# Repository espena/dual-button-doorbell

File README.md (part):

# Dual-button doorbell

*V. 1.2*

A door bell that simply does more. Configurable with alarms, different sounds for the two buttons, bedtime LED indicator and timed notifications on specific days / hours. With audible 4Ω loudspeaker driven by a class D 3.2 W amplifier.

The project is described on my [home page](https://espenandersen.no/dual-button-doorbell/).

## Features

- Two-button interface with led indicators
- Personalized doorbell sound from custom wav files
- Cron calendar for scheduling sounds down to one second resolution
- SD card support for storing audio files and configuration
- WiFi interface with integrated antenna
- MQTT support for smart home integration and push notifications
- Battery backed-up real-time clock
- Time automatically set over the network using NTP
- Can be configured to use custom time zones
- Silent mode with alternate bell sounds during night hours
- Relay for triggering external doorbell along with custom sound
- Accepts AC or DC power input from existing doorbell power supplies

## Circuit

Custom symbols, footprints and 3D models can be found in [espena/kicad-libs](https://github.com/espena/kicad-libs) whenever they're ready.

## Firmware

Written in C/C++ using [FreeRTOS](https://www.freertos.org/) and [ESP-IDF](https://docs.espressif.com/projects/esp-idf/en/latest/esp32/get-started/). Additionally I use the brilliant [ccronexpr](https://github.com/staticlibs/ccronexpr) C library for parsing the cron-alike sound schedule. Source code is located in the [firmware/dual-button-doorbell](firmware/dual-button-doorbell) folder within this repository.

## Configuration

Configuration and assets must be stored on the SD card. See [/firmware/dual-button-doorbell/sdcard](/firmware/dual-button-doorbell/sdcard) for an example configuration.

## Button panel

## Panel back side enclosure

```stl
solid Mesh
  facet normal 0.000000 1.000000 0.000000
    outer loop
      vertex 50.000000 30.000000 0.000000
      vertex -50.000000 30.000000 0.000000
      vertex -50.000000 30.000000 19.000000
    endloop
  endfacet
  facet normal 0.000000 1.000000 -0.000000
    outer loop
      vertex 50.000000 30.000000 0.000000
      vertex -50.000000 30.000000 19.000000
      vertex 50.000000 30.000000 19.000000
    endloop
  endfacet
  facet normal -1.000000 -0.000000 0.000000
    outer loop
      vertex -50.000000 30.000000 19.000000
      vertex -50.000000 -30.000000 0.000000
      vertex -50.000000 -30.000000 19.000000
    endloop
  endfacet
  facet normal -1.000000 0.000000 0.000000
    outer loop
      vertex -50.000000 30.000000 0.000000
      vertex -50.000000 -30.000000 0.000000
      vertex -50.000000 30.000000 19.000000
    endloop
  endfacet
  facet normal 1.000000 -0.000000 0.000000
    outer loop
      vertex 50.000000 -30.000000 19.000000
      vertex 50.000000 30.000000 0.000000
      vertex 50.000000 30.000000 19.000000
    endloop
  endfacet
  facet normal 1.000000 0.000000 0.000000
    outer loop
      vertex 50.000000 -30.000000 0.000000
      vertex 50.000000 30.000000 0.000000
      vertex 50.000000 -30.000000 19.000000
    endloop
  endfacet
  facet normal 0.000000 0.000000 -1.000000
    outer loop
      vertex -48.000000 -28.000000 0.000000
      vertex -50.000000 30.000000 0.000000
      vertex -48.000000 28.000000 0.000000
    endloop
  endfacet
  facet normal 0.000000 0.000000 -1.000000
    outer loop
      vertex -50.000000 -30.000000 0.000000
      vertex -50.000000 30.000000 0.000000
      vertex -48.000000 -28.000000 0.000000
    endloop
  endfacet
  facet normal 0.000000 0.000000 -1.000000
    outer loop
      vertex -50.000000 -30.000000 0.000000
      vertex 48.000000 -28.000000 0.000000
      vertex 50.000000 -30.000000 0.000000
    endloop
  endfacet
  facet normal 0.000000 -0.000000 -1.000000
    outer loop
      vertex -48.000000 -28.000000 0.000000
      vertex 48.000000 -28.000000 0.000000
      vertex -50.000000 -30.000000 0.000000
    endloop
  endfacet
  facet normal 0.000000 0.000000 -1.000000
    outer loop
      vertex 48.000000 28.000000 0.000000
      vertex 50.000000 30.000000 0.000000
      vertex 48.000000 -28.000000 0.000000
    endloop
  endfacet
  facet normal 0.000000 0.000000 -1.000000
    outer loop
      vertex 48.000000 -28.000000 0.000000
      vertex 50.000000 30.000000 0.000000
      vertex 50.000000 -30.000000 0.000000
    endloop
  endfacet
  facet normal 0.000000 0.000000 -1.000000
    outer loop
      vertex -50.000000 30.000000 0.000000
      vertex 50.000000 30.000000 0.000000
      vertex -48.000000 28.000000 0.000000
    endloop
  endfacet
  facet normal 0.000000 0.000000 -1.000000
    outer loop
      vertex -48.000000 28.000000 0.000000
      vertex 50.000000 30.000000 0.000000
      vertex 48.000000 28.000000 0.000000
    endloop
  endfacet
  facet normal 0.000000 0.000000 1.000000
    outer loop
      vertex -29.796875 -7.549917 19.000000
      vertex -50.000000 -30.000000 19.000000
      vertex -29.410429 -7.946122 19.000000
    endloop
  endfacet
  facet normal 0.000000 0.000000 1.000000
    outer loop
      vertex -29.004713 -8.322572 19.000000
      vertex -29.410429 -7.946122 19.000000
      vertex -50.000000 -30.000000 19.000000
    endloop
  endfacet
  facet normal 0.000000 0.000000 1.000000
    outer loop
      vertex -30.163094 -7.134943 19.000000
      vertex -50.000000 -30.000000 19.000000
      vertex -29.796875 -7.549917 19.000000
    endloop
  endfacet
  facet normal 0.000000 0.000000 1.000000
    outer loop
      vertex -28.580736 -8.678329 19.000000
      vertex -29.004713 -8.322572 19.000000
      vertex -50.000000 -30.000000 19.000000
    endloop
  endfacet
  facet normal 0.000000 0.000000 1.000000
    outer loop
      vertex -30.508171 -6.702229 19.000000
      vertex -50.000000 -30.000000 19.000000
      vertex -30.163094 -7.134943 19.000000
    endloop
  endfacet
  facet normal 0.000000 0.000000 1.000000
    outer loop
      vertex -28.139555 -9.012512 19.000000
      vertex -28.580736 -8.678329 19.000000
      vertex -50.000000 -30.000000 19.000000
    endloop
  endfacet
  facet normal 0.000000 0.000000 1.000000
    outer loop
      vertex -30.831251 -6.252852 19.000000
      vertex -50.000000 -30.000000 19.000000
      vertex -30.508171 -6.702229 19.000000
    endloop
  endfacet
  facet normal 0.000000 0.000000 1.000000
    outer loop
      vertex -27.682264 -9.324287 19.000000
      vertex -28.139555 -9.012512 19.000000
      vertex -50.000000 -30.000000 19.000000
    endloop
  endfacet
  facet normal 0.000000 0.000000 1.000000
    outer loop
      vertex -31.131529 -5.787931 19.000000
      vertex -50.000000 -30.000000 19.000000
      vertex -30.831251 -6.252852 19.000000
    endloop
  endfacet
  facet normal 0.000000 0.000000 1.000000
    outer loop
      vertex -27.209999 -9.612882 19.000000
      vertex -27.682264 -9.324287 19.000000
      vertex -50.000000 -30.000000 19.000000
    endloop
  endfacet
  facet normal 0.000000 0.000000 1.000000
    outer loop
      vertex -31.408260 -5.308619 19.000000
      vertex -50.000000 -30.000000 19.000000
      vertex -31.131529 -5.787931 19.000000
    endloop
  endfacet
  facet normal 0.000000 0.000000 1.000000
    outer loop
      vertex -26.723938 -9.877577 19.000000
      vertex -27.209999 -9.612882 19.000000
      vertex -50.000000 -30.000000 19.000000
    endloop
  endfacet
  facet normal 0.000000 0.000000 1.000000
    outer loop
      vertex -31.660755 -4.816110 19.000000
      vertex -50.000000 -30.000000 19.000000
      vertex -31.408260 -5.308619 19.000000
    endloop
  endfacet
  facet normal 0.000000 0.000000 1.000000
    outer loop
      vertex -26.225286 -10.117715 19.000000
      vertex -26.723938 -9.877577 19.000000
      vertex -50.000000 -30.000000 19.000000
    endloop
  endfacet
  facet normal 0.000000 0.000000 1.000000
    outer loop
      vertex -31.888386 -4.311626 19.000000
      vertex -50.000000 -30.000000 19.000000
      vertex -31.660755 -4.816110 19.000000
    endloop
  endfacet
  facet normal 0.000000 0.000000 1.000000
    outer loop
      vertex -25.715286 -10.332699 19.000000
      vertex -26.225286 -10.117715 19.000000
      vertex -50.000000 -30.000000 19.000000
    endloop
  endfacet
  facet normal 0.000000 0.000000 1.000000
    outer loop
      vertex -32.090588 -3.796424 19.000000
      vertex -50.000000 -30.000000 19.000000
      vertex -31.888386 -4.311626 19.000000
    endloop
  endfacet
  facet normal 0.000000 0.000000 1.000000
    outer loop
      vertex -25.195202 -10.521994 19.000000
      vertex -25.715286 -10.332699 19.000000
      vertex -50.000000 -30.000000 19.000000
    endloop
  endfacet
  facet normal 0.000000 0.000000 1.000000
    outer loop
      vertex -32.266857 -3.271782 19.000000
      vertex -50.000000 -30.000000 19.000000
      vertex -32.090588 -3.796424 19.000000
    endloop
  endfacet
  facet normal 0.000000 0.000000 1.000000
    outer loop
      vertex -24.666328 -10.685129 19.000000
      vertex -25.195202 -10.521994 19.000000
      vertex -50.000000 -30.000000 19.000000
    endloop
  endfacet
  facet normal 0.000000 0.000000 1.000000
    outer loop
      vertex -32.416759 -2.739007 19.000000
      vertex -50.000000 -30.000000 19.000000
      vertex -32.266857 -3.271782 19.000000
    endloop
  endfacet
  facet normal 0.000000 0.000000 1.000000
    outer loop
      vertex -24.129982 -10.821700 19.000000
      vertex -24.666328 -10.685129 19.000000
      vertex -50.000000 -30.000000 19.000000
    endloop
  endfacet
  facet normal 0.000000 0.000000 1.000000
    outer loop
      vertex -32.539913 -2.199422 19.000000
      vertex -50.000000 -30.000000 19.000000
      vertex -32.416759 -2.739007 19.000000
    endloop
  endfacet
  facet normal 0.000000 0.000000 1.000000
    outer loop
      vertex -23.587494 -10.931366 19.000000
      vertex -24.129982 -10.821700 19.000000
      vertex -50.000000 -30.000000 19.000000
    endloop
  endfacet
  facet normal 0.000000 0.000000 1.000000
    outer loop
      vertex -32.636021 -1.654369 19.000000
      vertex -50.000000 -30.000000 19.000000
      vertex -32.539913 -2.199422 19.000000
    endloop
  endfacet
  facet normal 0.000000 0.000000 1.000000
    outer loop
      vertex -23.040215 -11.013855 19.000000
      vertex -23.587494 -10.931366 19.000000
      vertex -50.000000 -30.000000 19.000000
    endloop
  endfacet
  facet normal 0.000000 0.000000 1.000000
    outer loop
      vertex -32.704842 -1.105203 19.000000
      vertex -50.000000 -30.000000 19.000000
      vertex -32.636021 -1.654369 19.000000
    endloop
  endfacet
  facet normal 0.000000 0.000000 1.000000
    outer loop
      vertex -22.489504 -11.068962 19.000000
      vertex -23.040215 -11.013855 19.000000
      vertex -50.000000 -30.000000 19.000000
    endloop
  endfacet
  facet normal 0.000000 0.000000 1.000000
    outer loop
      vertex -32.746201 -0.553289 19.000000
      vertex -50.000000 -30.000000 19.000000
      vertex -32.704842 -1.105203 19.000000
    endloop
  endfacet
  facet normal 0.000000 0.000000 1.000000
    outer loop
      vertex -21.936731 -11.096550 19.000000
      vertex -22.489504 -11.068962 19.000000
      vertex -50.000000 -30.000000 19.000000
    endloop
  endfacet
  facet normal 0.000000 0.000000 1.000000
    outer loop
      vertex -32.759998 0.000000 19.000000
      vertex -50.000000 -30.000000 19.000000
      vertex -32.746201 -0.553289 19.000000
    endloop
  endfacet
  facet normal 0.000000 0.000000 1.000000
    outer loop
      vertex -21.383270 -11.096550 19.000000
      vertex -21.936731 -11.096550 19.000000
      vertex -50.000000 -30.000000 19.000000
    endloop
  endfacet
  facet normal 0.000000 0.000000 1.000000
    outer loop
      vertex -20.830496 -11.068962 19.000000
      vertex -21.383270 -11.096550 19.000000
      vertex -50.000000 -30.000000 19.000000
    endloop
  endfacet
  facet normal 0.000000 0.000000 1.000000
    outer loop
      vertex -20.279785 -11.013855 19.000000
      vertex -20.830496 -11.068962 19.000000
      vertex -50.000000 -30.000000 19.000000
    endloop
  endfacet
  facet normal 0.000000 0.000000 1.000000
    outer loop
      vertex -19.732506 -10.931366 19.000000
      vertex -20.279785 -11.013855 19.000000
      vertex -50.000000 -30.000000 19.000000
    endloop
  endfacet
  facet normal 0.000000 0.000000 1.000000
    outer loop
      vertex -19.190018 -10.821700 19.000000
      vertex -19.732506 -10.931366 19.000000
      vertex -50.000000 -30.000000 19.000000
    endloop
  endfacet
  facet normal 0.000000 0.000000 1.000000
    outer loop
      vertex -18.653671 -10.685129 19.000000
      vertex -19.190018 -10.821700 19.000000
      vertex -50.000000 -30.000000 19.000000
    endloop
  endfacet
  facet normal 0.000000 0.000000 1.000000
    outer loop
      vertex -50.000000 30.000000 19.000000
      vertex -50.000000 -30.000000 19.000000
      vertex -32.759998 0.000000 19.000000
    endloop
  endfacet
  facet normal 0.000000 0.000000 1.000000
    outer loop
      vertex -50.000000 30.000000 19.000000
      vertex -32.759998 0.000000 19.000000
      vertex -32.746201 0.553289 19.000000
    endloop
  endfacet
  facet normal 0.000000 0.000000 1.000000
    outer loop
      vertex -50.000000 30.000000 19.000000
      vertex -32.746201 0.553289 19.000000
      vertex -32.704842 1.105203 19.000000
    endloop
  endfacet
  facet normal 0.000000 0.000000 1.000000
    outer loop
      vertex -50.000000 30.000000 19.000000
      vertex -32.704842 1.105203 19.000000
      vertex -32.636021 1.654369 19.000000
    endloop
  endfacet
  facet normal 0.000000 0.000000 1.000000
    outer loop
      vertex -50.000000 30.000000 19.000000
      vertex -32.636021 1.654369 19.000000
      vertex -32.539913 2.199422 19.000000
    endloop
  endfacet
  facet normal 0.000000 0.000000 1.000000
    outer loop
      vertex -50.000000 30.000000 19.000000
      vertex -32.539913 2.199422 19.000000
      vertex -32.416759 2.739007 19.000000
    endloop
  endfacet
  facet normal 0.000000 0.000000 1.000000
    outer loop
      vertex -50.000000 30.000000 19.000000
      vertex -32.416759 2.739007 19.000000
      vertex -32.266857 3.271782 19.000000
    endloop
  endfacet
  facet normal 0.000000 0.000000 1.000000
    outer loop
      vertex -50.000000 30.000000 19.000000
      vertex -32.266857 3.271782 19.000000
      vertex -32.090588 3.796424 19.000000
    endloop
  endfacet
  facet normal 0.000000 0.000000 1.000000
    outer loop
      vertex -50.000000 30.000000 19.000000
      vertex -32.090588 3.796424 19.000000
      vertex -31.888386 4.311626 19.000000
    endloop
  endfacet
  facet normal 0.000000 0.000000 1.000000
    outer loop
      vertex -50.000000 30.000000 19.000000
      vertex -31.888386 4.311626 19.000000
      vertex -31.660755 4.816110 19.000000
    endloop
  endfacet
  facet normal 0.000000 0.000000 1.000000
    outer loop
      vertex -50.000000 30.000000 19.000000
      vertex -31.660755 4.816110 19.000000
      vertex -31.408260 5.308619 19.000000
    endloop
  endfacet
  facet normal 0.000000 0.000000 1.000000
    outer loop
      vertex -50.000000 30.000000 19.000000
      vertex -31.408260 5.308619 19.000000
      vertex -31.131529 5.787931 19.000000
    endloop
  endfacet
  facet normal 0.000000 0.000000 1.000000
    outer loop
      vertex -50.000000 30.000000 19.000000
      vertex -31.131529 5.787931 19.000000
      vertex -30.831251 6.252852 19.000000
    endloop
  endfacet
  facet normal 0.000000 0.000000 1.000000
    outer loop
      vertex -50.000000 30.000000 19.000000
      vertex -30.831251 6.252852 19.000000
      vertex -30.508171 6.702229 19.000000
    endloop
  endfacet
  facet normal 0.000000 0.000000 1.000000
    outer loop
      vertex -50.000000 30.000000 19.000000
      vertex -30.508171 6.702229 19.000000
      vertex -30.163094 7.134943 19.000000
    endloop
  endfacet
  facet normal 0.000000 0.000000 1.000000
    outer loop
      vertex -50.000000 30.000000 19.000000
      vertex -30.163094 7.134943 19.000000
      vertex -29.796875 7.549917 19.000000
    endloop
  endfacet
  facet normal 0.000000 0.000000 1.000000
    outer loop
      vertex -50.000000 30.000000 19.000000
      vertex -29.796875 7.549917 19.000000
      vertex -29.410429 7.946122 19.000000
    endloop
  endfacet
  facet normal 0.000000 0.000000 1.000000
    outer loop
      vertex -50.000000 30.000000 19.000000
      vertex -29.410429 7.946122 19.000000
      vertex -29.004713 8.322572 19.000000
    endloop
  endfacet
  facet normal 0.000000 0.000000 1.000000
    outer loop
      vertex -28.580736 8.678329 19.000000
      vertex -50.000000 30.000000 19.000000
      vertex -29.004713 8.322572 19.000000
    endloop
  endfacet
  facet normal 0.000000 0.000000 1.000000
    outer loop
      vertex -28.139555 9.012512 19.000000
      vertex -50.000000 30.000000 19.000000
      vertex -28.580736 8.678329 19.000000
    endloop
  endfacet
  facet normal 0.000000 0.000000 1.000000
    outer loop
      vertex -27.682264 9.324287 19.000000
      vertex -50.000000 30.000000 19.000000
      vertex -28.139555 9.012512 19.000000
    endloop
  endfacet
  facet normal 0.000000 0.000000 1.000000
    outer loop
      vertex -27.209999 9.612882 19.000000
      vertex -50.000000 30.000000 19.000000
      vertex -27.682264 9.324287 19.000000
    endloop
  endfacet
  facet normal 0.000000 0.000000 1.000000
    outer loop
      vertex -26.723938 9.877577 19.000000
      vertex -50.000000 30.000000 19.000000
      vertex -27.209999 9.612882 19.000000
    endloop
  endfacet
  facet normal 0.000000 0.000000 1.000000
    outer loop
      vertex -26.225286 10.117715 19.000000
      vertex -50.000000 30.000000 19.000000
      vertex -26.723938 9.877577 19.000000
    endloop
  endfacet
  facet normal 0.000000 0.000000 1.000000
    outer loop
      vertex -25.715286 10.332699 19.000000
      vertex -50.000000 30.000000 19.000000
      vertex -26.225286 10.117715 19.000000
    endloop
  endfacet
  facet normal 0.000000 0.000000 1.000000
    outer loop
      vertex -25.195202 10.521994 19.000000
      vertex -50.000000 30.000000 19.000000
      vertex -25.715286 10.332699 19.000000
    endloop
  endfacet
  facet normal 0.000000 0.000000 1.000000
    outer loop
      vertex -24.666328 10.685129 19.000000
      vertex -50.000000 30.000000 19.000000
      vertex -25.195202 10.521994 19.000000
    endloop
  endfacet
  facet normal 0.000000 0.000000 1.000000
    outer loop
      vertex -24.129982 10.821700 19.000000
      vertex -50.000000 30.000000 19.000000
      vertex -24.666328 10.685129 19.000000
    endloop
  endfacet
  facet normal 0.000000 0.000000 1.000000
    outer loop
      vertex -23.587494 10.931366 19.000000
      vertex -50.000000 30.000000 19.000000
      vertex -24.129982 10.821700 19.000000
    endloop
  endfacet
  facet normal 0.000000 0.000000 1.000000
    outer loop
      vertex -23.040215 11.013855 19.000000
      vertex -50.000000 30.000000 19.000000
      vertex -23.587494 10.931366 19.000000
    endloop
  endfacet
  facet normal 0.000000 0.000000 1.000000
    outer loop
      vertex -22.489504 11.068962 19.000000
      vertex -50.000000 30.000000 19.000000
      vertex -23.040215 11.013855 19.000000
    endloop
  endfacet
  facet normal 0.000000 0.000000 1.000000
    outer loop
      vertex -21.936731 11.096550 19.000000
      vertex -50.000000 30.000000 19.000000
      vertex -22.489504 11.068962 19.000000
    endloop
  endfacet
  facet normal 0.000000 0.000000 1.000000
    outer loop
      vertex -21.383270 11.096550 19.000000
      vertex -50.000000 30.000000 19.000000
      vertex -21.936731 11.096550 19.000000
    endloop
  endfacet
  facet normal 0.000000 0.000000 1.000000
    outer loop
      vertex -20.830496 11.068962 19.000000
      vertex -50.000000 30.000000 19.000000
      vertex -21.383270 11.096550 19.000000
    endloop
  endfacet
  facet normal 0.000000 0.000000 1.000000
    outer loop
      vertex -20.279785 11.013855 19.000000
      vertex -50.000000 30.000000 19.000000
      vertex -20.830496 11.068962 19.000000
    endloop
  endfacet
  facet normal 0.000000 0.000000 1.000000
    outer loop
      vertex -19.732506 10.931366 19.000000
      vertex -50.000000 30.000000 19.000000
      vertex -20.279785 11.013855 19.000000
    endloop
  endfacet
  facet normal 0.000000 0.000000 1.000000
    outer loop
      vertex -19.190018 10.821700 19.000000
      vertex -50.000000 30.000000 19.000000
      vertex -19.732506 10.931366 19.000000
    endloop
  endfacet
  facet normal 0.000000 0.000000 1.000000
    outer loop
      vertex 13.522124 -7.549917 19.000000
      vertex -13.909572 -7.946122 19.000000
      vertex 13.908571 -7.946122 19.000000
    endloop
  endfacet
  facet normal 0.000000 0.000000 1.000000
    outer loop
      vertex 13.522124 -7.549917 19.000000
      vertex -13.523125 -7.549917 19.000000
      vertex -13.909572 -7.946122 19.000000
    endloop
  endfacet
  facet normal 0.000000 0.000000 1.000000
    outer loop
      vertex 14.314287 -8.322572 19.000000
      vertex 13.908571 -7.946122 19.000000
      vertex -13.909572 -7.946122 19.000000
    endloop
  endfacet
  facet normal 0.000000 0.000000 1.000000
    outer loop
      vertex 14.314287 -8.322572 19.000000
      vertex -13.909572 -7.946122 19.000000
      vertex -14.315288 -8.322572 19.000000
    endloop
  endfacet
  facet normal 0.000000 0.000000 1.000000
    outer loop
      vertex 14.314287 -8.322572 19.000000
      vertex -14.315288 -8.322572 19.000000
      vertex -14.739264 -8.678329 19.000000
    endloop
  endfacet
  facet normal 0.000000 0.000000 1.000000
    outer loop
      vertex 13.155907 -7.134943 19.000000
      vertex -12.811830 -6.702229 19.000000
      vertex -13.156907 -7.134943 19.000000
    endloop
  endfacet
  facet normal 0.000000 0.000000 1.000000
    outer loop
      vertex 13.155907 -7.134943 19.000000
      vertex -13.156907 -7.134943 19.000000
      vertex -13.523125 -7.549917 19.000000
    endloop
  endfacet
  facet normal 0.000000 0.000000 1.000000
    outer loop
      vertex 13.155907 -7.134943 19.000000
      vertex -13.523125 -7.549917 19.000000
      vertex 13.522124 -7.549917 19.000000
    endloop
  endfacet
  facet normal 0.000000 0.000000 1.000000
    outer loop
      vertex 14.738263 -8.678329 19.000000
      vertex 14.314287 -8.322572 19.000000
      vertex -14.739264 -8.678329 19.000000
    endloop
  endfacet
  facet normal 0.000000 0.000000 1.000000
    outer loop
      vertex 12.810829 -6.702229 19.000000
      vertex -12.811830 -6.702229 19.000000
      vertex 13.155907 -7.134943 19.000000
    endloop
  endfacet
  facet normal 0.000000 0.000000 1.000000
    outer loop
      vertex 15.179445 -9.012512 19.000000
      vertex -14.739264 -8.678329 19.000000
      vertex -15.180446 -9.012512 19.000000
    endloop
  endfacet
  facet normal 0.000000 0.000000 1.000000
    outer loop
      vertex 15.179445 -9.012512 19.000000
      vertex -15.180446 -9.012512 19.000000
      vertex -15.637736 -9.324287 19.000000
    endloop
  endfacet
  facet normal 0.000000 0.000000 1.000000
    outer loop
      vertex 15.179445 -9.012512 19.000000
      vertex 14.738263 -8.678329 19.000000
      vertex -14.739264 -8.678329 19.000000
    endloop
  endfacet
  facet normal 0.000000 0.000000 1.000000
    outer loop
      vertex 12.487750 -6.252852 19.000000
      vertex -12.488750 -6.252852 19.000000
      vertex -12.811830 -6.702229 19.000000
    endloop
  endfacet
  facet normal 0.000000 0.000000 1.000000
    outer loop
      vertex 12.487750 -6.252852 19.000000
      vertex -12.811830 -6.702229 19.000000
      vertex 12.810829 -6.702229 19.000000
    endloop
  endfacet
  facet normal 0.000000 0.000000 1.000000
    outer loop
      vertex 15.636737 -9.324287 19.000000
      vertex 15.179445 -9.012512 19.000000
      vertex -15.637736 -9.324287 19.000000
    endloop
  endfacet
  facet normal 0.000000 0.000000 1.000000
    outer loop
      vertex 12.187471 -5.787931 19.000000
      vertex -11.911740 -5.308619 19.000000
      vertex -12.188471 -5.787931 19.000000
    endloop
  endfacet
  facet normal 0.000000 0.000000 1.000000
    outer loop
      vertex 12.187471 -5.787931 19.000000
      vertex -12.188471 -5.787931 19.000000
      vertex -12.488750 -6.252852 19.000000
    endloop
  endfacet
  facet normal 0.000000 0.000000 1.000000
    outer loop
      vertex 12.187471 -5.787931 19.000000
      vertex -12.488750 -6.252852 19.000000
      vertex 12.487750 -6.252852 19.000000
    endloop
  endfacet
  facet normal 0.000000 0.000000 1.000000
    outer loop
      vertex 16.108999 -9.612882 19.000000
      vertex -15.637736 -9.324287 19.000000
      vertex -16.110001 -9.612882 19.000000
    endloop
  endfacet
  facet normal 0.000000 0.000000 1.000000
    outer loop
      vertex 16.108999 -9.612882 19.000000
      vertex 15.636737 -9.324287 19.000000
      vertex -15.637736 -9.324287 19.000000
    endloop
  endfacet
  facet normal 0.000000 0.000000 1.000000
    outer loop
      vertex 11.910741 -5.308619 19.000000
      vertex -11.911740 -5.308619 19.000000
      vertex 12.187471 -5.787931 19.000000
    endloop
  endfacet
  facet normal 0.000000 0.000000 1.000000
    outer loop
      vertex 16.595062 -9.877577 19.000000
      vertex 16.108999 -9.612882 19.000000
      vertex -16.110001 -9.612882 19.000000
    endloop
  endfacet
  facet normal 0.000000 0.000000 1.000000
    outer loop
      vertex 16.595062 -9.877577 19.000000
      vertex -16.110001 -9.612882 19.000000
      vertex -16.596062 -9.877577 19.000000
    endloop
  endfacet
  facet normal 0.000000 0.000000 1.000000
    outer loop
      vertex 11.658246 -4.816110 19.000000
      vertex -11.659245 -4.816110 19.000000
      vertex -11.911740 -5.308619 19.000000
    endloop
  endfacet
  facet normal 0.000000 0.000000 1.000000
    outer loop
      vertex 11.658246 -4.816110 19.000000
      vertex -11.911740 -5.308619 19.000000
      vertex 11.910741 -5.308619 19.000000
    endloop
  endfacet
  facet normal 0.000000 0.000000 1.000000
    outer loop
      vertex 17.093714 -10.117715 19.000000
      vertex -16.596062 -9.877577 19.000000
      vertex -17.094713 -10.117715 19.000000
    endloop
  endfacet
  facet normal 0.000000 0.000000 1.000000
    outer loop
      vertex 17.093714 -10.117715 19.000000
      vertex 16.595062 -9.877577 19.000000
      vertex -16.596062 -9.877577 19.000000
    endloop
  endfacet
  facet normal 0.000000 0.000000 1.000000
    outer loop
      vertex 11.430614 -4.311626 19.000000
      vertex -11.431614 -4.311626 19.000000
      vertex -11.659245 -4.816110 19.000000
    endloop
  endfacet
  facet normal 0.000000 0.000000 1.000000
    outer loop
      vertex 11.430614 -4.311626 19.000000
      vertex -11.659245 -4.816110 19.000000
      vertex 11.658246 -4.816110 19.000000
    endloop
  endfacet
  facet normal 0.000000 0.000000 1.000000
    outer loop
      vertex 17.603714 -10.332699 19.000000
      vertex -17.094713 -10.117715 19.000000
      vertex -17.604715 -10.332699 19.000000
    endloop
  endfacet
  facet normal 0.000000 0.000000 1.000000
    outer loop
      vertex 17.603714 -10.332699 19.000000
      vertex 17.093714 -10.117715 19.000000
      vertex -17.094713 -10.117715 19.000000
    endloop
  endfacet
  facet normal 0.000000 0.000000 1.000000
    outer loop
      vertex 11.228412 -3.796424 19.000000
      vertex -11.053142 -3.271782 19.000000
      vertex -11.229412 -3.796424 19.000000
    endloop
  endfacet
  facet normal 0.000000 0.000000 1.000000
    outer loop
      vertex 11.228412 -3.796424 19.000000
      vertex -11.229412 -3.796424 19.000000
      vertex -11.431614 -4.311626 19.000000
    endloop
  endfacet
  facet normal 0.000000 0.000000 1.000000
    outer loop
      vertex 11.228412 -3.796424 19.000000
      vertex -11.431614 -4.311626 19.000000
      vertex 11.430614 -4.311626 19.000000
    endloop
  endfacet
  facet normal 0.000000 0.000000 1.000000
    outer loop
      vertex 18.123798 -10.521994 19.000000
      vertex -17.604715 -10.332699 19.000000
      vertex -18.124798 -10.521994 19.000000
    endloop
  endfacet
  facet normal 0.000000 0.000000 1.000000
    outer loop
      vertex 18.123798 -10.521994 19.000000
      vertex 17.603714 -10.332699 19.000000
      vertex -17.604715 -10.332699 19.000000
    endloop
  endfacet
  facet normal 0.000000 0.000000 1.000000
    outer loop
      vertex 11.052142 -3.271782 19.000000
      vertex -11.053142 -3.271782 19.000000
      vertex 11.228412 -3.796424 19.000000
    endloop
  endfacet
  facet normal 0.000000 0.000000 1.000000
    outer loop
      vertex 18.652670 -10.685129 19.000000
      vertex -18.124798 -10.521994 19.000000
      vertex -18.653671 -10.685129 19.000000
    endloop
  endfacet
  facet normal 0.000000 0.000000 1.000000
    outer loop
      vertex 18.652670 -10.685129 19.000000
      vertex -18.653671 -10.685129 19.000000
      vertex -50.000000 -30.000000 19.000000
    endloop
  endfacet
  facet normal 0.000000 0.000000 1.000000
    outer loop
      vertex 18.652670 -10.685129 19.000000
      vertex 18.123798 -10.521994 19.000000
      vertex -18.124798 -10.521994 19.000000
    endloop
  endfacet
  facet normal 0.000000 0.000000 1.000000
    outer loop
      vertex 10.902242 -2.739007 19.000000
      vertex -10.903242 -2.739007 19.000000
      vertex -11.053142 -3.271782 19.000000
    endloop
  endfacet
  facet normal 0.000000 0.000000 1.000000
    outer loop
      vertex 10.902242 -2.739007 19.000000
      vertex -11.053142 -3.271782 19.000000
      vertex 11.052142 -3.271782 19.000000
    endloop
  endfacet
  facet normal 0.000000 0.000000 1.000000
    outer loop
      vertex 10.779085 -2.199422 19.000000
      vertex -10.780086 -2.199422 19.000000
      vertex -10.903242 -2.739007 19.000000
    endloop
  endfacet
  facet normal 0.000000 0.000000 1.000000
    outer loop
      vertex 10.779085 -2.199422 19.000000
      vertex -10.903242 -2.739007 19.000000
      vertex 10.902242 -2.739007 19.000000
    endloop
  endfacet
  facet normal 0.000000 0.000000 1.000000
    outer loop
      vertex 10.682978 -1.654369 19.000000
      vertex -10.683978 -1.654369 19.000000
      vertex -10.780086 -2.199422 19.000000
    endloop
  endfacet
  facet normal 0.000000 0.000000 1.000000
    outer loop
      vertex 10.682978 -1.654369 19.000000
      vertex -10.780086 -2.199422 19.000000
      vertex 10.779085 -2.199422 19.000000
    endloop
  endfacet
  facet normal 0.000000 0.000000 1.000000
    outer loop
      vertex 10.614159 -1.105203 19.000000
      vertex -10.573798 -0.553289 19.000000
      vertex -10.615158 -1.105203 19.000000
    endloop
  endfacet
  facet normal 0.000000 0.000000 1.000000
    outer loop
      vertex 10.614159 -1.105203 19.000000
      vertex -10.615158 -1.105203 19.000000
      vertex -10.683978 -1.654369 19.000000
    endloop
  endfacet
  facet normal 0.000000 0.000000 1.000000
    outer loop
      vertex 10.614159 -1.105203 19.000000
      vertex -10.683978 -1.654369 19.000000
      vertex 10.682978 -1.654369 19.000000
    endloop
  endfacet
  facet normal 0.000000 0.000000 1.000000
    outer loop
      vertex 10.572798 -0.553289 19.000000
      vertex -10.573798 -0.553289 19.000000
      vertex 10.614159 -1.105203 19.000000
    endloop
  endfacet
  facet normal 0.000000 0.000000 1.000000
    outer loop
      vertex 10.559000 0.000000 19.000000
      vertex -10.573798 -0.553289 19.000000
      vertex 10.572798 -0.553289 19.000000
    endloop
  endfacet
  facet normal 0.000000 0.000000 1.000000
    outer loop
      vertex 10.559000 0.000000 19.000000
      vertex -10.560000 0.000000 19.000000
      vertex -10.573798 -0.553289 19.000000
    endloop
  endfacet
  facet normal 0.000000 0.000000 1.000000
    outer loop
      vertex 10.572798 0.553289 19.000000
      vertex -10.573798 0.553289 19.000000
      vertex -10.560000 0.000000 19.000000
    endloop
  endfacet
  facet normal 0.000000 0.000000 1.000000
    outer loop
      vertex 10.572798 0.553289 19.000000
      vertex -10.560000 0.000000 19.000000
      vertex 10.559000 0.000000 19.000000
    endloop
  endfacet
  facet normal 0.000000 0.000000 1.000000
    outer loop
      vertex 10.614159 1.105203 19.000000
      vertex -10.683978 1.654369 19.000000
      vertex -10.615158 1.105203 19.000000
    endloop
  endfacet
  facet normal 0.000000 0.000000 1.000000
    outer loop
      vertex 10.614159 1.105203 19.000000
      vertex -10.615158 1.105203 19.000000
      vertex -10.573798 0.553289 19.000000
    endloop
  endfacet
  facet normal 0.000000 0.000000 1.000000
    outer loop
      vertex 10.614159 1.105203 19.000000
      vertex -10.573798 0.553289 19.000000
      vertex 10.572798 0.553289 19.000000
    endloop
  endfacet
  facet normal 0.000000 0.000000 1.000000
    outer loop
      vertex 10.682978 1.654369 19.000000
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
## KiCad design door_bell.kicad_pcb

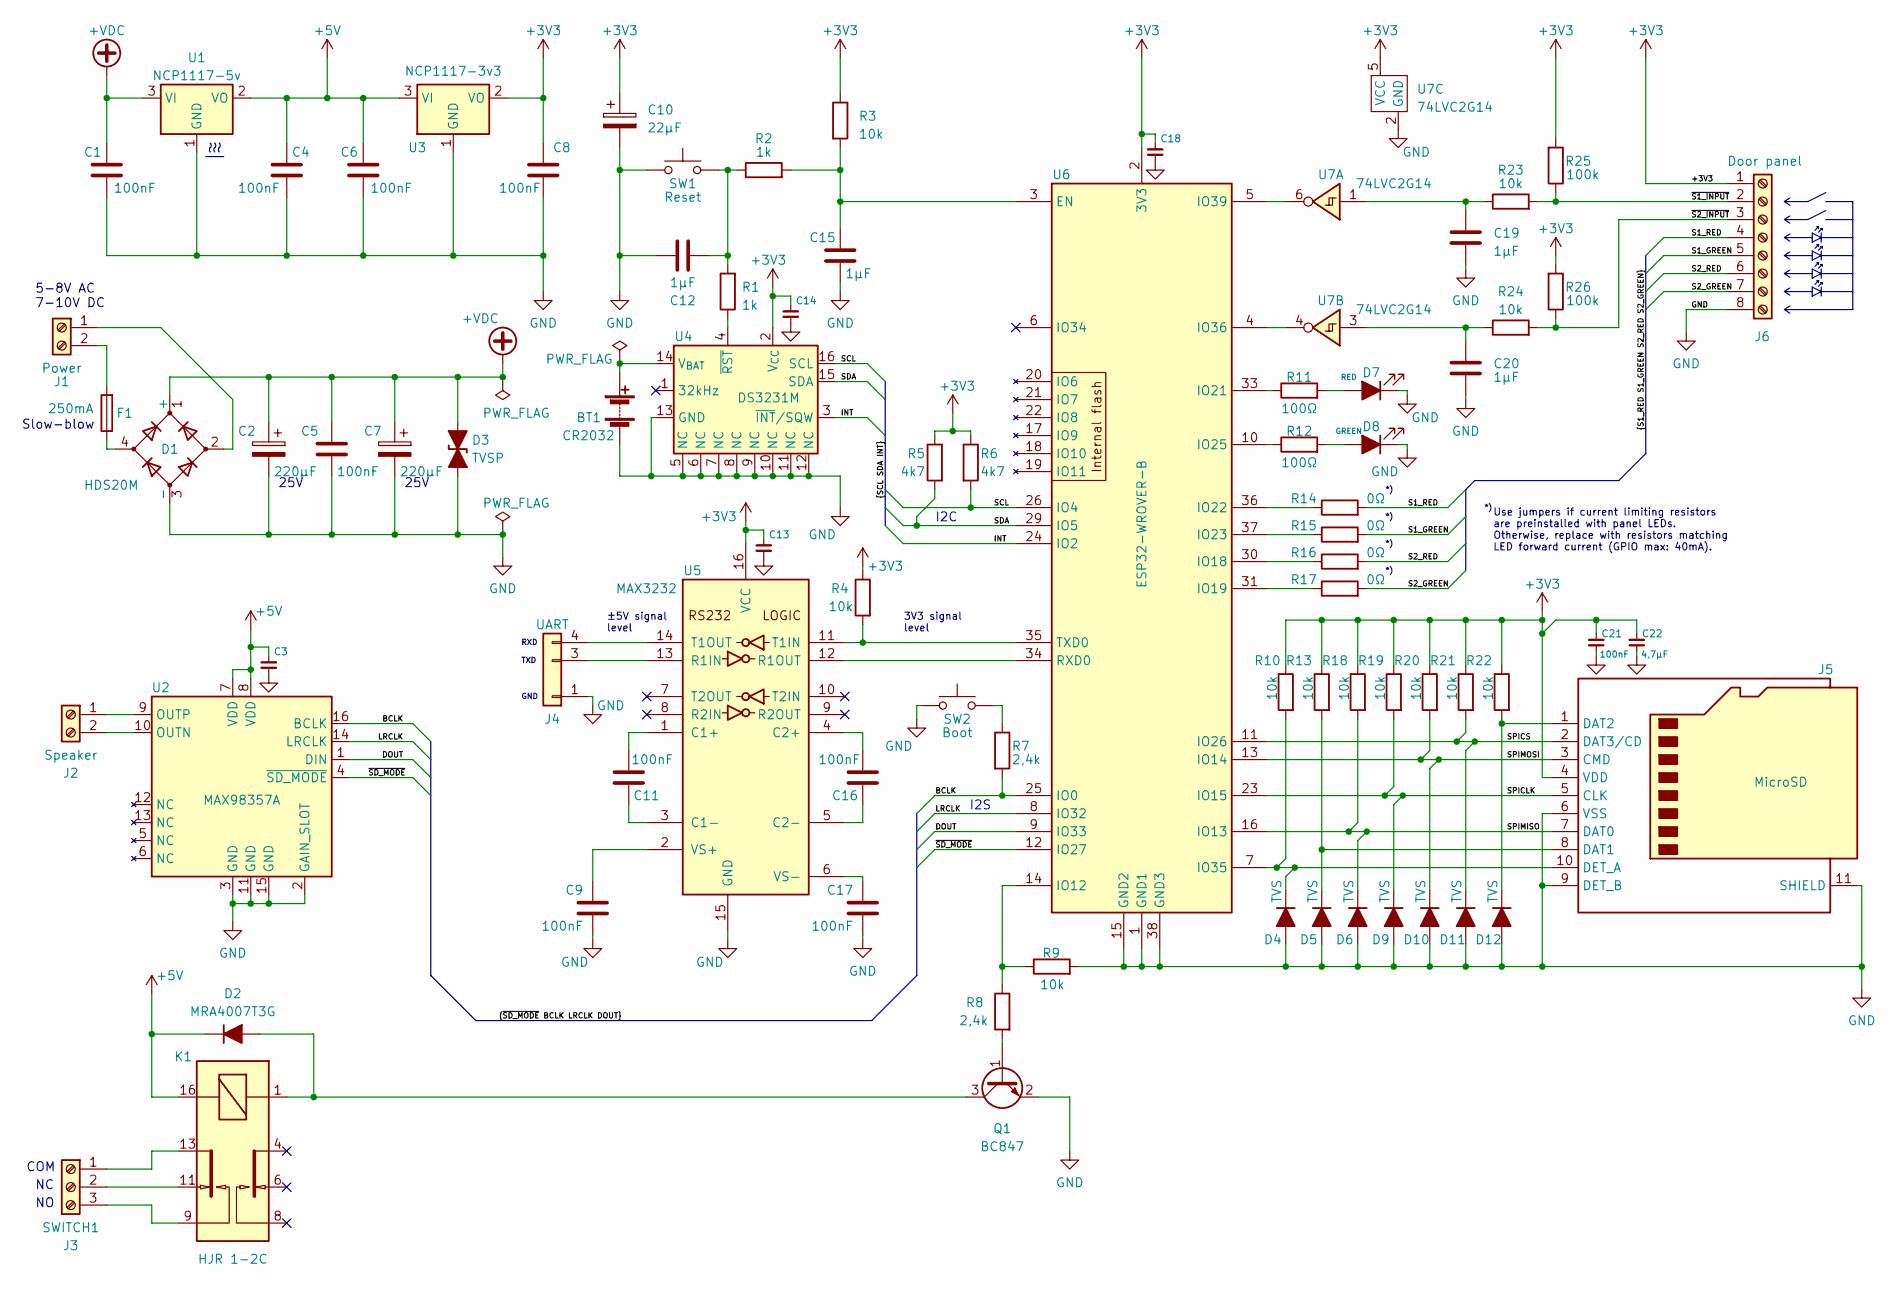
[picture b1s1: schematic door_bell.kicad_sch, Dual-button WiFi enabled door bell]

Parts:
BT1: CR2032; BatteryHolder_Keystone_1058_1x2032
C1, C4, C5, C6, C8, C9, C11, C16, C17, C21: 100nF; C_0805_2012Metric_Pad1.18x1.45mm_HandSolder
C2, C7: 220µF; CP_Elec_6.3x9.9
C3, C13, C14, C18: C_Decoupling; C_0805_2012Metric_Pad1.18x1.45mm_HandSolder
C10: 22µF; C_0805_2012Metric_Pad1.18x1.45mm_HandSolder
C12, C15, C19, C20: 1µF; C_0805_2012Metric_Pad1.18x1.45mm_HandSolder
C22: 4,7µF; C_0805_2012Metric_Pad1.18x1.45mm_HandSolder
D1: HDS20M; D_HDS20M_Rectifier
D2: MRA4007T3G; D_SMB_Handsoldering
D3: TVSP; DO-214AA-2
D4, D5, D6, D9, D10, D11, D12: TVS; D_SOD-523
D7: RED; LED_0805_2012Metric_Pad1.15x1.40mm_HandSolder
D8: GREEN; LED_0805_2012Metric_Pad1.15x1.40mm_HandSolder
F1: 250mA; FuseHolder_Keystone_3554
J1: Power; TerminalBlock_Phoenix_PT-1,5-2-3.5-H_1x02_P3.50mm_Horizonta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
J2: Speaker; TerminalBlock_Phoenix_PT-1,5-2-3.5-H_1x02_P3.50mm_Horizonta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
J3: SWITCH1; TerminalBlock_Phoenix_PT-1,5-3-3.5-H_1x03_P3.50mm_Horizonta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
J4: UART; PinHeader_1x04_P1.27mm_Vertical_without_pin2
J5: MicroSD; microSD_HC_Hirose_DM3AT-SF-PEJM5
J6: Door panel; TerminalBlock_Phoenix_PT-1,5-8-3.5-H_1x08_P3.50mm_Horizonta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
K1: HJR 1-2C; Relay_Tianbo_HJR-1-2C
Q1: BC847; SOT-23
R1, R2: 1k; R_0805_2012Metric_Pad1.20x1.40mm_HandSolder
R3, R4, R9, R10, R13, R18, R19, R20, R21, R22, R23, R24: 10k; R_0805_2012Metric_Pad1.20x1.40mm_HandSolder
R5, R6: 4k7; R_0805_2012Metric_Pad1.20x1.40mm_HandSolder
R7, R8: 2,4k; R_0805_2012Metric_Pad1.20x1.40mm_HandSolder
R11, R12: 100Ω; R_0805_2012Metric_Pad1.20x1.40mm_HandSolder
R14, R15, R16, R17: 0Ω; R_0805_2012Metric_Pad1.20x1.40mm_HandSolder
R25, R26: 100k; R_0805_2012Metric_Pad1.20x1.40mm_HandSolder
SW1: Reset; SW_SPST_TL3301_6x6mm_H4.3mm
SW2: Boot; SW_SPST_TL3301_6x6mm_H4.3mm
U1: NCP1117-5v; SOT-223-3_TabPin2_ThermalPads_Heatsink_x2
U2: MAX98357A; TQFN-16-1EP_3x3mm_P0.5mm_EP1.23x1.23mm
U3: NCP1117-3v3; SOT-223-3_TabPin2_ThermalPads
U4: DS3231M; SOIC-16W_7.5x10.3mm_P1.27mm
U5: MAX3232; TSSOP-16-1EP_4.4x5mm_P0.65mm
U6: ESP32-WROVER-B
U7: 74LVC2G14; TSOT-23-6

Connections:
+3V3: C8.1, C10.1, C13.1, C14.2, C18.1, C21.1, C22.1, J5.4 (VDD), J6.1, R3.1, R4.1, R5.1, R6.1, R10.1, R13.1, R18.1, R19.1, R20.1, R21.1, R22.1, R25.2, R26.2, U3.2 (VO), U4.2 (V_{CC}), U5.16 (VCC), U6.2 (3V3), U7.5 (VCC)
+5V: C3.1, C4.1, C6.1, D2.1 (K), K1.16, U1.2 (VO), U2.7 (VDD), U2.8 (VDD), U3.3 (VI)
+VDC: C1.1, C2.1, C5.1, C7.1, D1.1 (+), D3.2 (A2), U1.3 (VI)
/BCLK: R7.2, U2.16 (BCLK), U6.25 (IO0)
/DOUT: U2.1 (DIN), U6.9 (IO33)
/INT: U4.3 (~INT/SQW), U6.24 (IO2)
/LRCLK: U2.14 (LRCLK), U6.8 (IO32)
/S1_GREEN: J6.5, R15.2
/S1_RED: J6.4, R14.2
/S2_GREEN: J6.7, R17.2
/S2_RED: J6.6, R16.2
/SCL: R6.2, U4.16 (SCL), U6.26 (IO4)
/SDA: R5.2, U4.15 (SDA), U6.29 (IO5)
/SPICLK: D9.1 (K), J5.5 (CLK), R19.2, U6.23 (IO15)
/SPICS: D11.1 (K), J5.2 (DAT3/CD), R21.2, U6.11 (IO26)
/SPIMISO: D6.1 (K), J5.7 (DAT0), R18.2, U6.16 (IO13)
/SPIMOSI: D10.1 (K), J5.3 (CMD), R20.2, U6.13 (IO14)
/~S1_INPUT: J6.2, R23.2, R25.1
/~S2_INPUT: J6.3, R24.2, R26.1
/~SD_MODE: U2.4 (~SD_MODE), U6.12 (IO27)
GND: BT1.2 (-), C1.2, C2.2, C3.2, C4.2, C5.2, C6.2, C7.2, C8.2, C9.2, C10.2, C12.1, C13.2, C14.1, C15.2, C17.2, C18.2, C19.2, C20.2, C21.2, C22.2, D1.3 (-), D3.1 (A1), D4.2 (A), D5.2 (A), D6.2 (A), D7.1 (K), D8.1 (K), D9.2 (A), D10.2 (A), D11.2 (A), D12.2 (A), J4.1, J5.6 (VSS), J5.9 (DET_B), J5.11 (SHIELD), J6.8, Q1.2 (E), R9.2, SW1.1, SW2.1, U1.1 (GND), U2.2 (GAIN_SLOT), U2.3 (GND), U2.11 (GND), U2.15 (GND), U3.1 (GND), U4.5 (NC), U4.6 (NC), U4.7 (NC), U4.8 (NC), U4.9 (NC), U4.10 (NC), U4.11 (NC), U4.12 (NC), U4.13 (GND), U5.15 (GND), U6.1 (GND1), U6.15 (GND2), U6.38 (GND3), U7.2 (GND)
unnamed: BT1.1 (+), U4.14 (V_{BAT})
unnamed: C12.2, R1.2, R2.1, SW1.2
unnamed: C19.1, R23.1, U7.1
unnamed: C20.1, R24.1, U7.3
unnamed: D1.4, F1.1
unnamed: D2.2 (A), K1.1, Q1.3 (C)
unnamed: D4.1 (K), J5.10 (DET_A), R10.2, U6.7 (IO35)
unnamed: D5.1 (K), J5.8 (DAT1), R13.2
unnamed: D7.2 (A), R11.2
unnamed: D8.2 (A), R12.2
unnamed: D12.1 (K), J5.1 (DAT2), R22.2
unnamed: D1.2, J1.1
unnamed: F1.2, J1.2
unnamed: J2.1, U2.9 (OUTP)
unnamed: J2.2, U2.10 (OUTN)
unnamed: J3.1, K1.13
unnamed: J3.2, K1.11
unnamed: J3.3, K1.9
unnamed: J4.3, U5.13 (R1IN)
unnamed: J4.4, U5.14 (T1OUT)
unnamed: Q1.1 (B), R8.2
unnamed: R7.1, SW2.2
unnamed: R1.1, U4.4 (~RST)
unnamed: C11.1, U5.1 (C1+)
unnamed: C11.2, U5.3 (C1-)
unnamed: C16.1, U5.4 (C2+)
unnamed: C16.2, U5.5 (C2-)
unnamed: U5.12 (R1OUT), U6.34 (RXD0)
unnamed: R4.2, U5.11 (T1IN), U6.35 (TXD0)
unnamed: C9.1, U5.2 (VS+)
unnamed: C17.1, U5.6 (VS-)
unnamed: C15.1, R2.2, R3.2, U6.3 (EN)
unnamed: R8.1, R9.1, U6.14 (IO12)
unnamed: R16.1, U6.30 (IO18)
unnamed: R17.1, U6.31 (IO19)
unnamed: R11.1, U6.33 (IO21)
unnamed: R14.1, U6.36 (IO22)
unnamed: R15.1, U6.37 (IO23)
unnamed: R12.1, U6.10 (IO25)
unnamed: U6.4 (IO36), U7.4
unnamed: U6.5 (IO39), U7.6

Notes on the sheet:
TXD
RXD
3V3 signal level
GND
±5V signal level
25V
COM
I2S
Use jumpers if current limiting resistors are preinstalled with panel LEDs. Otherwise, replace with resistors matching LED forward current (GPIO max: 40mA).
5-8V AC 7-10V DC
Slow-blow
I2C

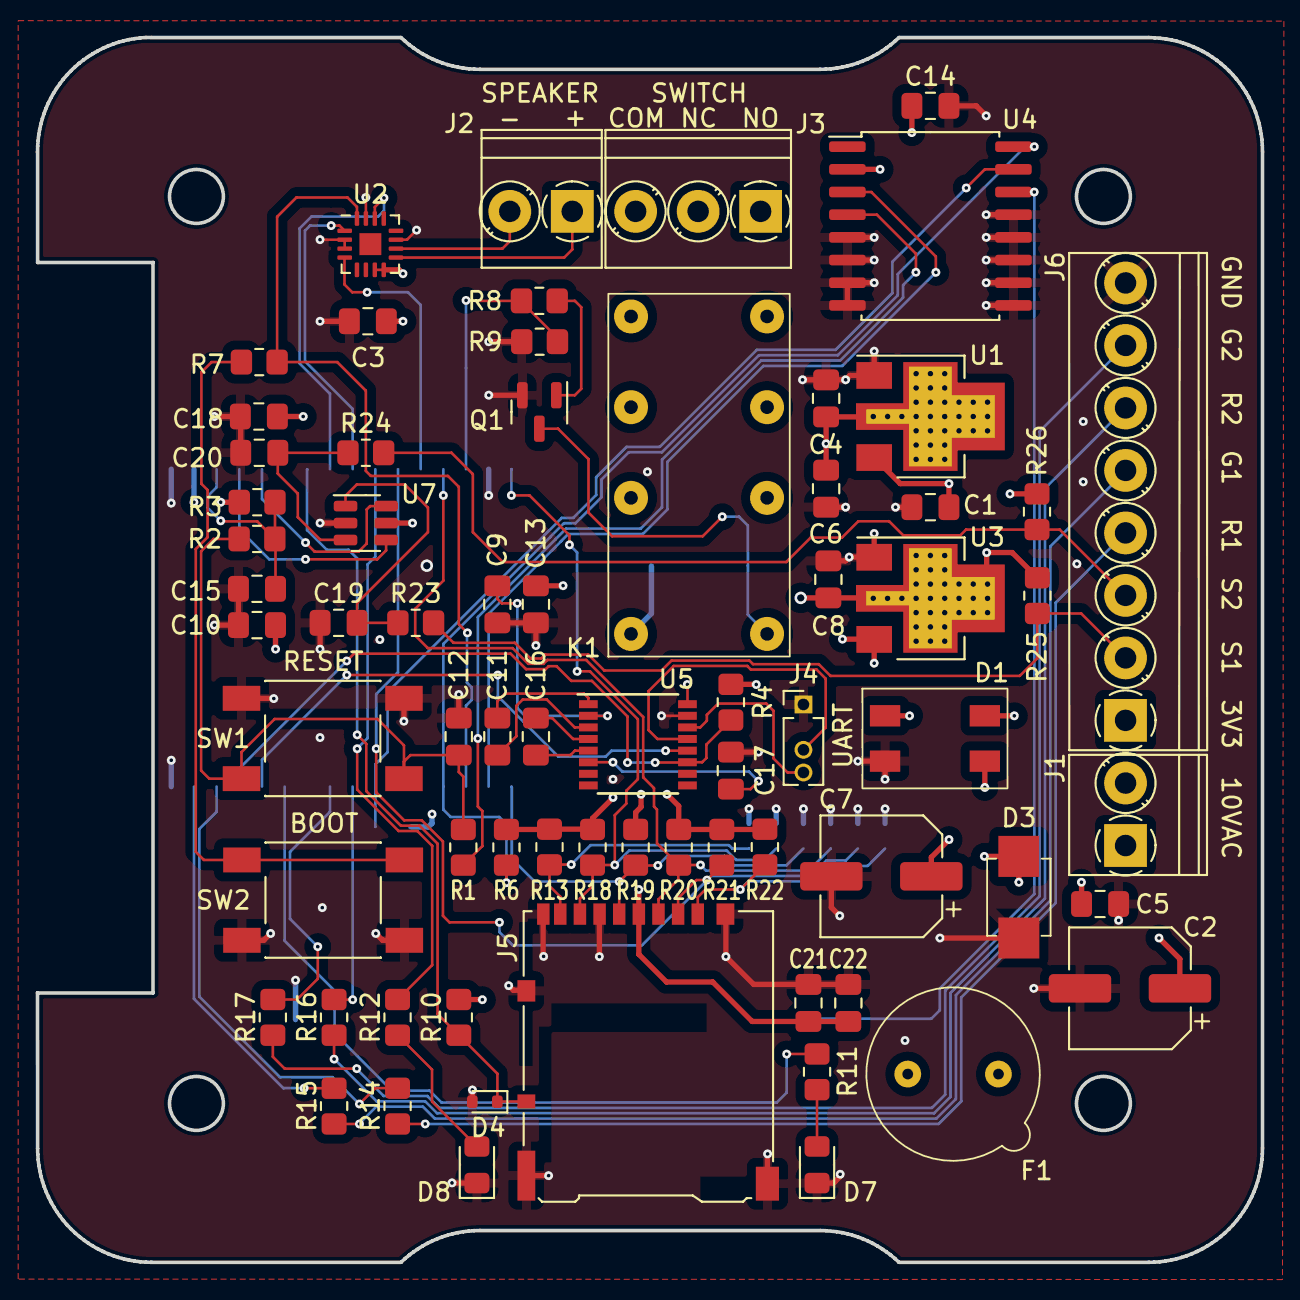
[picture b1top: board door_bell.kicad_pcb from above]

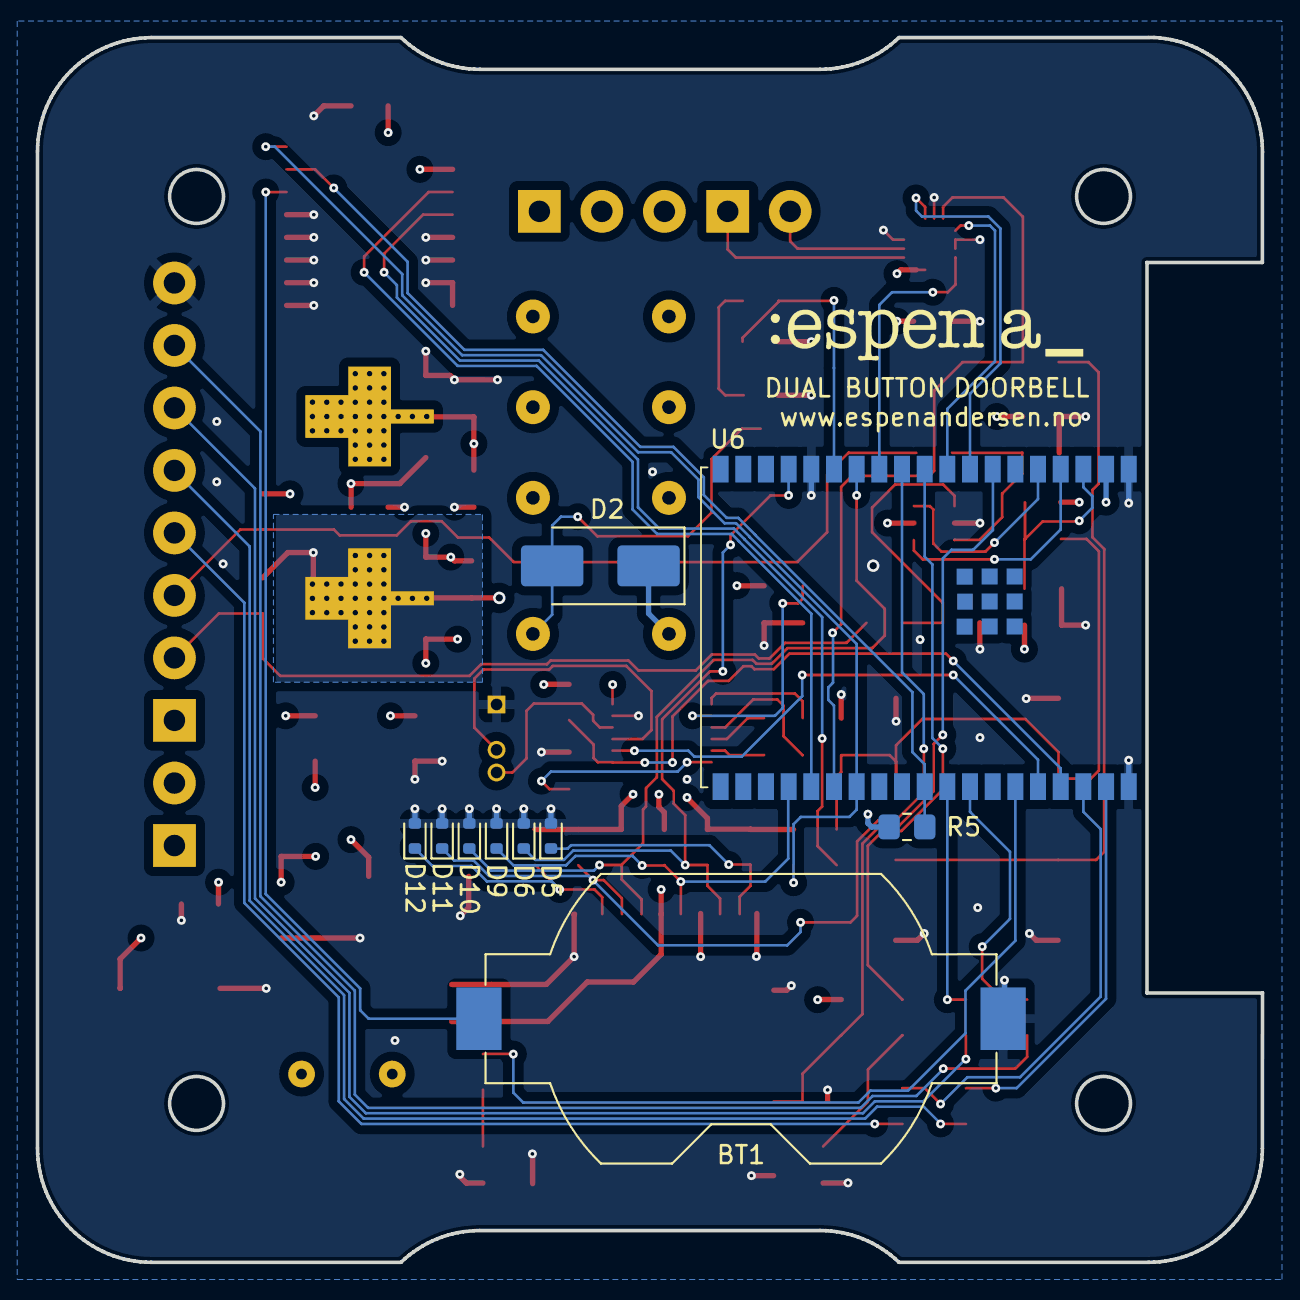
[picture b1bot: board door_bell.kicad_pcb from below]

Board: 4 copper layers, 68.6 x 68.6 mm, 79 parts (10 on the bottom side), 62 nets.

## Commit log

2023-05-21 Initial
2023-05-21 Update annotations
2023-05-21 Exclude backup copies from repo
2023-05-21 Add README
2023-05-21 Update README.md
    Add warning.
2023-05-21 Update README.md
    Minor edit.
2023-05-22 Assign footprint for fuse
2023-05-27 Part placement
2023-05-27 Part placement and silk screen adjustments
2023-05-27 Exclude autosave files
2023-05-27 Silk screen adjustments
2023-05-27 Adapting after placing 3D model of fuse F1
2023-05-27 Setting up footprints and 3D models
2023-05-27 Add PCB rendering to project description
2023-05-28 Add features
2023-05-28 Add subtitle
2023-05-28 Add 'Planned' to 'Fetures' subtitle
2023-05-28 Fix typo
2023-05-28 Update PCB with 3D model for ESP32
2023-05-28 Show both sides of PCB
2023-05-28 Update schematics
2023-05-28 Adjust layout
2023-05-28 Remove autosave artifacts
2023-05-28 Ignore autosave artifacts
2023-05-28 Add 3D model for bridge rectifier
2023-05-29 Start routing power rails
2023-05-29 Rip-up and retry ...
2023-05-29 GND plane routing
2023-05-30 Initial routing of power rails and some signals
2023-05-30 Update project description
2023-05-30 Fix board outline in QCAD and re-import to KiCad
2023-05-30 Done routing
2023-05-31 Gerber files sent to JLCPCB
2023-05-31 New 3D rendering with tracks
2023-05-31 Prototype finished, sent to production
2023-06-01 Add BOM with Mouser part references
2023-06-01 Omit Excel backup files
2023-06-01 Update BOM, add enclosure and speaker
2023-06-01 Change to alternative voltage regulator types
2023-06-03 Add 3D model of frontpanel back enclosure
2023-06-03 Add STL file
2023-06-03 Increase wall thickness to 2 mm
2023-06-03 Add front panel design to README
2023-06-03 Redact titles
2023-06-03 Add ASCII STL to README
2023-06-03 Try file include instead of embedding
2023-06-03 Revert
2023-06-03 Tidy up file/dir structure
2023-06-04 Update README.md
    Correct subtitle.
2023-06-11 Add MCU pad configuration
2023-06-11 Redraw, v.1.1 - fix errors
2023-06-11 Set table alignment
2023-06-11 Smaller title
2023-06-11 Enhance clarity in title
2023-06-11 Initial commit, ESP32 source code
2023-06-11 Do not include vscode donfigurations
2023-06-11 Reallocate pads for LEDS and Panel buttons
2023-06-11 GPIO 39/36 is input only, swap with 21/25 from panel button inputs
2023-06-11 Move .vscode to top level .gitignore
2023-06-11 Update schematics, altered MCU pin configuration
2023-06-14 Replace image with finished result
2023-06-14 User real-world image of door panel
2023-06-16 Initializing peripherals
2023-06-18 Swap to C++, begin app structuring
2023-06-18 Adding components and designing basic app structure
2023-06-18 Audo playback from sdcard now working
2023-06-19 Add event handling
2023-06-19 Implement non-blocking blink functionality
2023-06-19 Adjust event listener
2023-06-19 Fix spelling mistake
2023-06-19 Add pushbutton component
2023-06-19 Append button component
2023-06-19 Adding buttons to app
2023-06-19 Insert button settings into main application object
2023-06-19 Assert size for solidity
2023-06-21 Prepare components, tasks and events
2023-06-21 Update schematics, fix problems
2023-06-21 Replace TVS diodes with larger type (SOD-923 -> SOD-523)
2023-06-22 Rearrange i2s pin order to eliminate wire crossing
2023-06-22 Fix errors in board outline
2023-06-22 Update PCB with amended board outline
2023-06-23 Add TVS diode and note on panel LED resistors
2023-06-23 Change from IO2 to IO12 for relay
2023-06-24 Fix problem with WDT triggering during playback
2023-06-24 Reset PCB and remake component placement
2023-06-24 New layout
2023-06-24 Routing GND plane
2023-06-24 Routing power plane
2023-06-25 Routing complete
2023-06-25 Redering of new PCB, routing completed
2023-06-25 Revision 1.1 plotted and sent to factory
2023-06-25 Update PCB rendering
2023-06-27 Empty position in UART header to block connector if accidentially reversed
2023-06-27 Re-route connections to UART pin header
2023-06-27 Block buttons during playback
2023-06-27 Move traces away from hole
2023-06-28 Implement button LED indicators
2023-06-28 Correct implementation of WAV header
2023-06-28 Add IO for card detection
2023-06-29 Add component for reading user settings
2023-06-29 Implement user settings
2023-06-29 Discard legacy code
2023-06-29 Add header comment block
2023-07-01 Implement WiFi connection in separate task
2023-07-01 Adding SNTP support
2023-07-02 Correct text tag for UART
2023-07-02 Implement ntp class for date/time asynchronuous updates
2023-07-02 Provide static const for log tag strings
2023-07-02 Add default configuration for ntp service
2023-07-02 Update NTP settings from user file
2023-07-02 Increase network connection retries and improve log output
2023-07-02 Initial boilerplate for cron service
2023-07-02 Edit features list, adding AC/DC power input
2023-07-04 Working the cron component
2023-07-05 Cron loop implemented
2023-07-05 Add sdkconfig to repo
2023-07-05 Set up proper partition table
2023-07-05 Revert to 25 cron entries max
2023-07-05 Workaround for memory leak bug in setenv() for ESP32
2023-07-05 Custom partition table (WROVER has 4MB memory)
2023-07-06 Cron-scripting of sound effects OK
2023-07-06 Remove redundant line
2023-07-06 Do sound playback asynchronous
2023-07-06 Assert flag for using localtime and not UTC
2023-07-06 Fix concurrency issue with playback
2023-07-06 Implement silent mode after specific hours
2023-07-07 Change TVS diodes for SD card to unipolar ones
2023-07-07 Adjust labels
2023-07-07 Fix bug after restructuring JSON format
2023-07-07 Remove reduntant file
2023-07-10 Let C9 return to GND, increase i2c pullups R5/R6
2023-07-10 PCB serial no longer corresponds to current schematic
2023-07-10 Implement support for RTC chip
2023-07-10 Connect DS3231 interrupt line
2023-07-10 Add GPIO 2 as RTC interrupt line
2023-07-10 Update with info on firmware
2023-07-10 Fix link
2023-07-10 Collapse to one paragraph
2023-07-10 Add decoupling for SD card
2023-07-10 Collapse into single paragraph
2023-07-10 Updated schematics, decoupling on SD card
2023-07-11 Use static_cast
2023-07-11 Add MQTT support
2023-07-11 Add settings for mqtt component
2023-07-11 Add defaults for mqtt component
2023-07-15 Adjust stack size
2023-07-15 Implement MQTT support
2023-07-15 Add connection diagram to panel terminal block
2023-07-15 Use chip MAC address as unique client_id
2023-07-15 Elevate task priority
2023-07-15 Change input voltage specification
2023-07-16 Start implement logging to SD card
2023-07-16 Update features list
2023-07-16 Implement logging to SD card
2023-07-16 Edit project description
2023-07-16 Add configuration instructions
2023-07-16 Pointer to example configuration
2023-07-17 Remove leftover no-connection flag
2023-07-17 Update date
2023-07-17 Corrected version
2023-07-17 Free cert buffer before allocating, in case get_cert() is called multiple times
2023-07-17 Straighten the language...
2023-07-17 Update BOM with price per assembly
2023-07-17 Nudge i2c pullups a bit
2023-07-21 Downscale fuse to 500 mA slow-blow after tests
2023-07-21 Changed fuse to 500 mA slow-blow
2023-07-23 Update README.md with reference home page
2023-07-27 Add enable/disable settings for mqtt and silent mode
2023-07-27 Continuous red button light when in silent mode
2023-07-27 Improve log message string
2023-07-27 Update with new parameters
2023-07-27 Correct spelling errors
2023-07-30 Rephrase bad English
2023-07-31 Downscale fuse F1 to 250 mA after testing
2023-08-03 Add http server
2023-08-03 Load system time from RTC at startup
2023-08-03 Working minimal HTTP server
2023-08-04 Web configurator template
2023-08-11 PCB artwork for version 1.2
    Implementing changes for new version. Added two decoupling capacitors to SD card, improved thermal relief for 5V regulator and connected RTC _INT/SQW pin from RTC. Copper pours on outer layers.
2023-08-11 Improve heat sink on 5V regulator
2023-08-11 Add thermal vias to 3v3 regulator
2023-08-12 Plots and drill file for v 1.2
2023-08-12 PCB 3165818C-Y5 sent to production
2023-08-12 Update PCB 3D rendering
2023-08-14 Increase request buffer for receiving POST queries
2023-08-24 Add heatsink to 5V regulator
2023-08-24 Add back side heatsink
2023-08-24 Add 'hot surface' symbol to 5V regulator
2023-08-24 Change 5V regulator footprint to dual-heatsink
2023-08-25 Display values for decoupling capacitors
2023-08-27 Change C10 to non-polarized
2023-08-28 Add version number
2023-10-29 Add custom ringtone override example
2023-10-29 Description for custom doorbell sound overrides
2023-10-29 Implement custom doorbell sound overrides
2023-10-29 Web configurator, POST handing etc.
2023-10-29 URL decode for web gui
2023-10-29 Recompile
2023-10-29 Fix bug - duration in secs, not ms
2023-10-30 Add bell to override mode
2024-06-22 Fix missing initializer
